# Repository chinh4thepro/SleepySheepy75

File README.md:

# SleepySheepy75

Making a keyboard cause im bored

## Hardware

Uses a soldered on rp2040 as the MCU
- 85x diodes for each switch (one extra for knob switch)
- 1x rotary encoder (EC11(E))
- 84x hotswap sockets
- 1x W25Q128JVS as flash rom
- 1x USB-C as connector 
- 2x buttons for "boot" selection
- Other stuff for electrical stuff

## Software

It is to be ported to QMK and be supported with VIA/VIAL

## Design

TODO - Probably going to happen when I get the pcb, case is going to be available in variety of materials

## Progress

- [x] Design the schematic (Done on 2023-09-08)
- [x] Come up with a name + Design logo (Done on 2023-10-07 (Scrapped on PCB though))
- [x] Design the PCB (Done on 2023-09-17)
- [ ] Order the PCB and its parts
- [ ] Construct PCB
- [ ] Port QMK + VIA/VIAL
- [ ] Design case for a 3d printer
- [ ] Design case for acrylic stacking
- [ ] Design case for metal CNC

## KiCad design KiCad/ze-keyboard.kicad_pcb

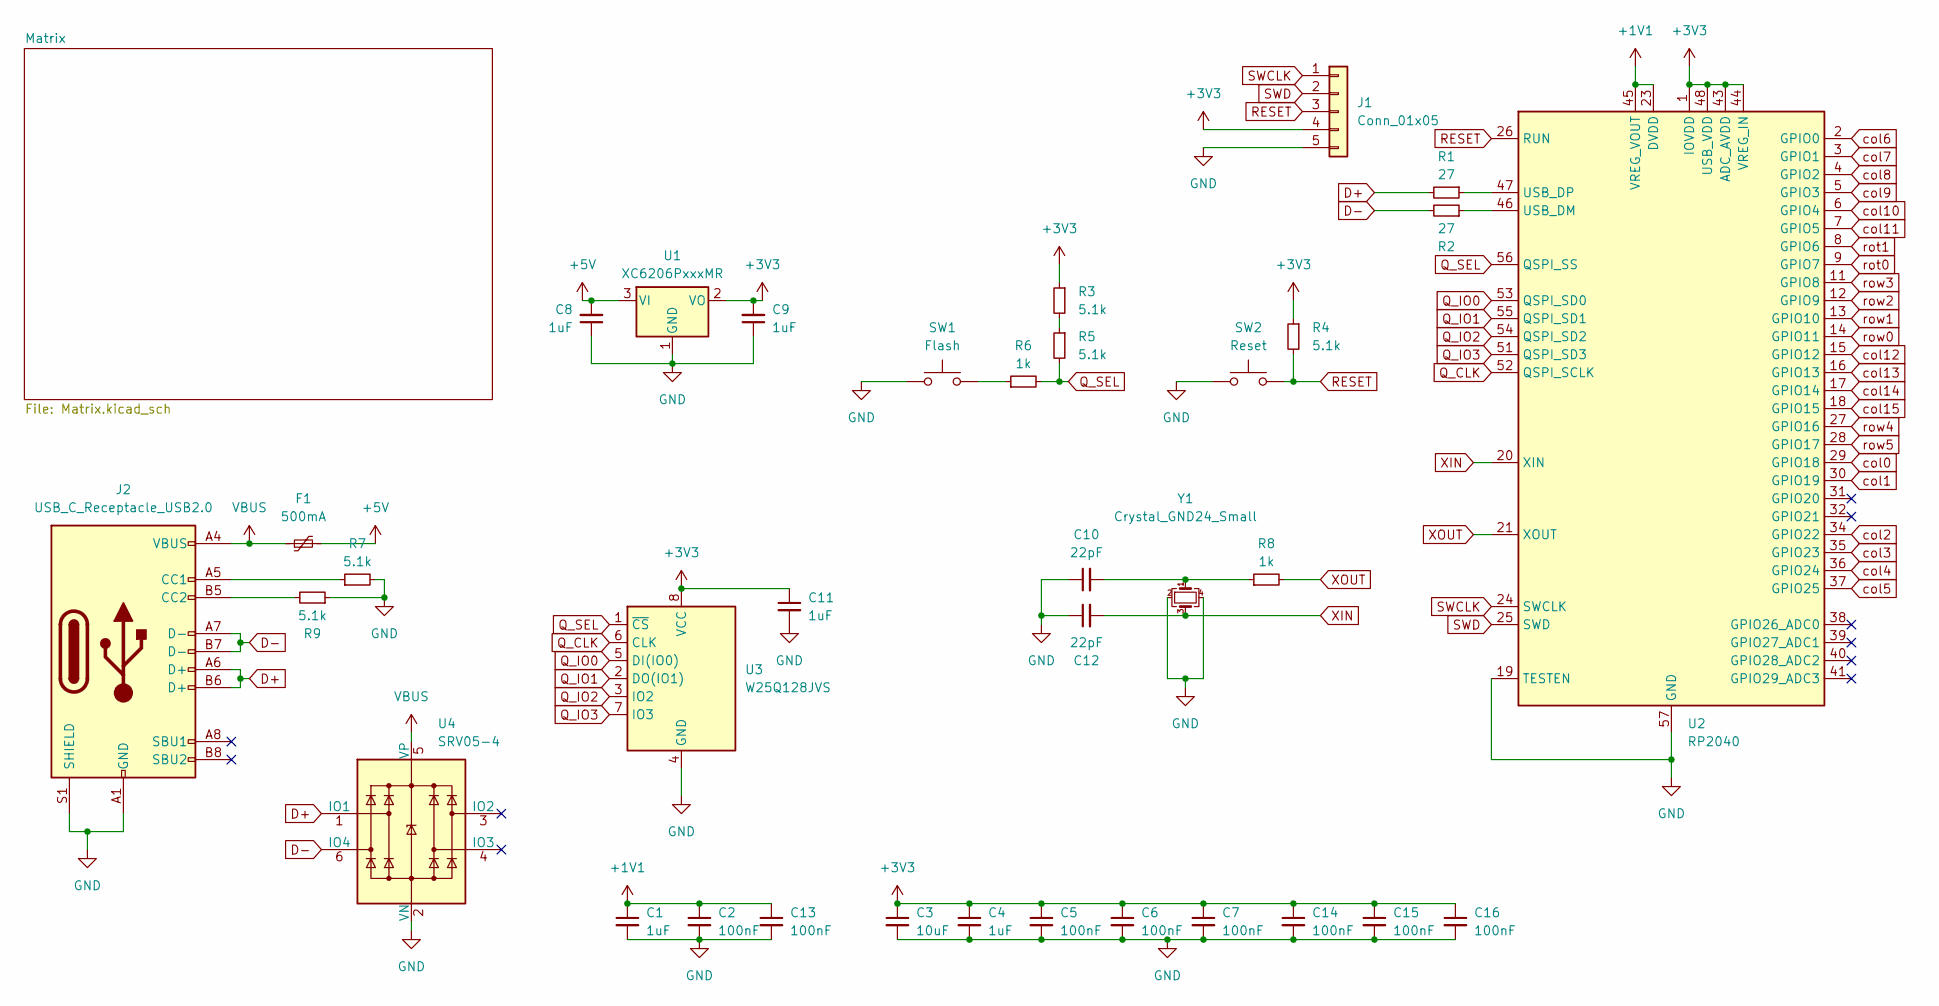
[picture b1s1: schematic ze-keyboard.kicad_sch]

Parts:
C1, C4, C8, C9, C11: 1uF; C_0402_1005Metric
C2, C5, C6, C7, C13, C14, C15, C16: 100nF; C_0402_1005Metric
C3: 10uF; C_0603_1608Metric
C10, C12: 22pF; C_0402_1005Metric
F1: 500mA; Fuse_1206_3216Metric
J1: Conn_01x05; PinHeader_1x05_P2.54mm_Vertical
J2: USB_C_Receptacle_USB2.0; USB_C_Receptacle_HRO_TYPE-C-31-M-12
R1, R2: 27; R_0402_1005Metric
R3, R4, R5, R7, R9: 5.1k; R_0402_1005Metric
R6, R8: 1k; R_0402_1005Metric
SW1: Flash; SW_SPST_TL3342
SW2: Reset; SW_SPST_TL3342
U1: XC6206PxxxMR; SOT-23-3
U2: RP2040; QFN-56-1EP_7x7mm_P0.4mm_EP3.2x3.2mm
U3: W25Q128JVS; SOIC-8_5.23x5.23mm_P1.27mm
U4: SRV05-4; SOT-23-6-routable
Y1: Crystal_GND24_Small; Crystal_SMD_3225-4Pin_3.2x2.5mm

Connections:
+1V1: C1.1, C2.1, C13.1, U2.23 (DVDD), U2.45 (VREG_VOUT), U2.50 (DVDD)
+3V3: C3.1, C4.1, C5.1, C6.1, C7.1, C9.2, C11.1, C14.1, C15.1, C16.1, J1.4, R3.1, R4.1, U1.2 (VO), U2.1 (IOVDD), U2.10 (IOVDD), U2.22 (IOVDD), U2.33 (IOVDD), U2.42 (IOVDD), U2.43 (ADC_AVDD), U2.44 (VREG_IN), U2.48 (USB_VDD), U2.49 (IOVDD), U3.8 (VCC)
+5V: C8.2, F1.2, U1.3 (VI); also elsewhere on the board
D+: J2.A6 (D+), J2.B6 (D+), R1.2, U4.1 (IO1)
D-: J2.A7 (D-), J2.B7 (D-), R2.2, U4.6 (IO4)
GND: C1.2, C2.2, C3.2, C4.2, C5.2, C6.2, C7.2, C8.1, C9.1, C10.1, C11.2, C12.1, C13.2, C14.2, C15.2, C16.2, J1.5, J2.A1 (GND), J2.A12 (GND), J2.B1 (GND), J2.B12 (GND), J2.S1 (SHIELD), R7.2, R9.1, SW1.1, SW2.1, U1.1 (GND), U2.19 (TESTEN), U2.57 (GND), U3.4 (GND), U4.2 (VN), Y1.2, Y1.4; also elsewhere on the board
unnamed: C10.2, R8.1, Y1.1
unnamed: J2.A5 (CC1), R7.1
unnamed: J2.B5 (CC2), R9.2
unnamed: R3.2, R5.1
unnamed: R6.1, SW1.2
unnamed: R2.1, U2.46 (USB_DM)
unnamed: R1.1, U2.47 (USB_DP)
Q_CLK: U2.52 (QSPI_SCLK), U3.6 (CLK)
Q_IO0: U2.53 (QSPI_SD0), U3.5 (DI(IO0))
Q_IO1: U2.55 (QSPI_SD1), U3.2 (DO(IO1))
Q_IO2: U2.54 (QSPI_SD2), U3.3 (IO2)
Q_IO3: U2.51 (QSPI_SD3), U3.7 (IO3)
Q_SEL: R5.2, R6.2, U2.56 (QSPI_SS), U3.1 (~CS)
RESET: J1.3, R4.2, SW2.2, U2.26 (RUN)
SWCLK: J1.1, U2.24 (SWCLK)
SWD: J1.2, U2.25 (SWD)
VBUS: F1.1, J2.A4 (VBUS), J2.A9 (VBUS), J2.B4 (VBUS), J2.B9 (VBUS), U4.5 (VP)
XIN: C12.2, U2.20 (XIN), Y1.3
XOUT: R8.2, U2.21 (XOUT)
col0: U2.29 (GPIO18); also elsewhere on the board
col1: U2.30 (GPIO19); also elsewhere on the board
col2: U2.34 (GPIO22); also elsewhere on the board
col3: U2.35 (GPIO23); also elsewhere on the board
col4: U2.36 (GPIO24); also elsewhere on the board
col5: U2.37 (GPIO25); also elsewhere on the board
col6: U2.2 (GPIO0); also elsewhere on the board
col7: U2.3 (GPIO1); also elsewhere on the board
col8: U2.4 (GPIO2); also elsewhere on the board
col9: U2.5 (GPIO3); also elsewhere on the board
col10: U2.6 (GPIO4); also elsewhere on the board
col11: U2.7 (GPIO5); also elsewhere on the board
col12: U2.15 (GPIO12); also elsewhere on the board
col13: U2.16 (GPIO13); also elsewhere on the board
col14: U2.17 (GPIO14); also elsewhere on the board
col15: U2.18 (GPIO15); also elsewhere on the board
row0: U2.14 (GPIO11); also elsewhere on the board
row1: U2.13 (GPIO10); also elsewhere on the board
row2: U2.12 (GPIO9); also elsewhere on the board
row3: U2.11 (GPIO8); also elsewhere on the board
row4: U2.27 (GPIO16); also elsewhere on the board
row5: U2.28 (GPIO17); also elsewhere on the board

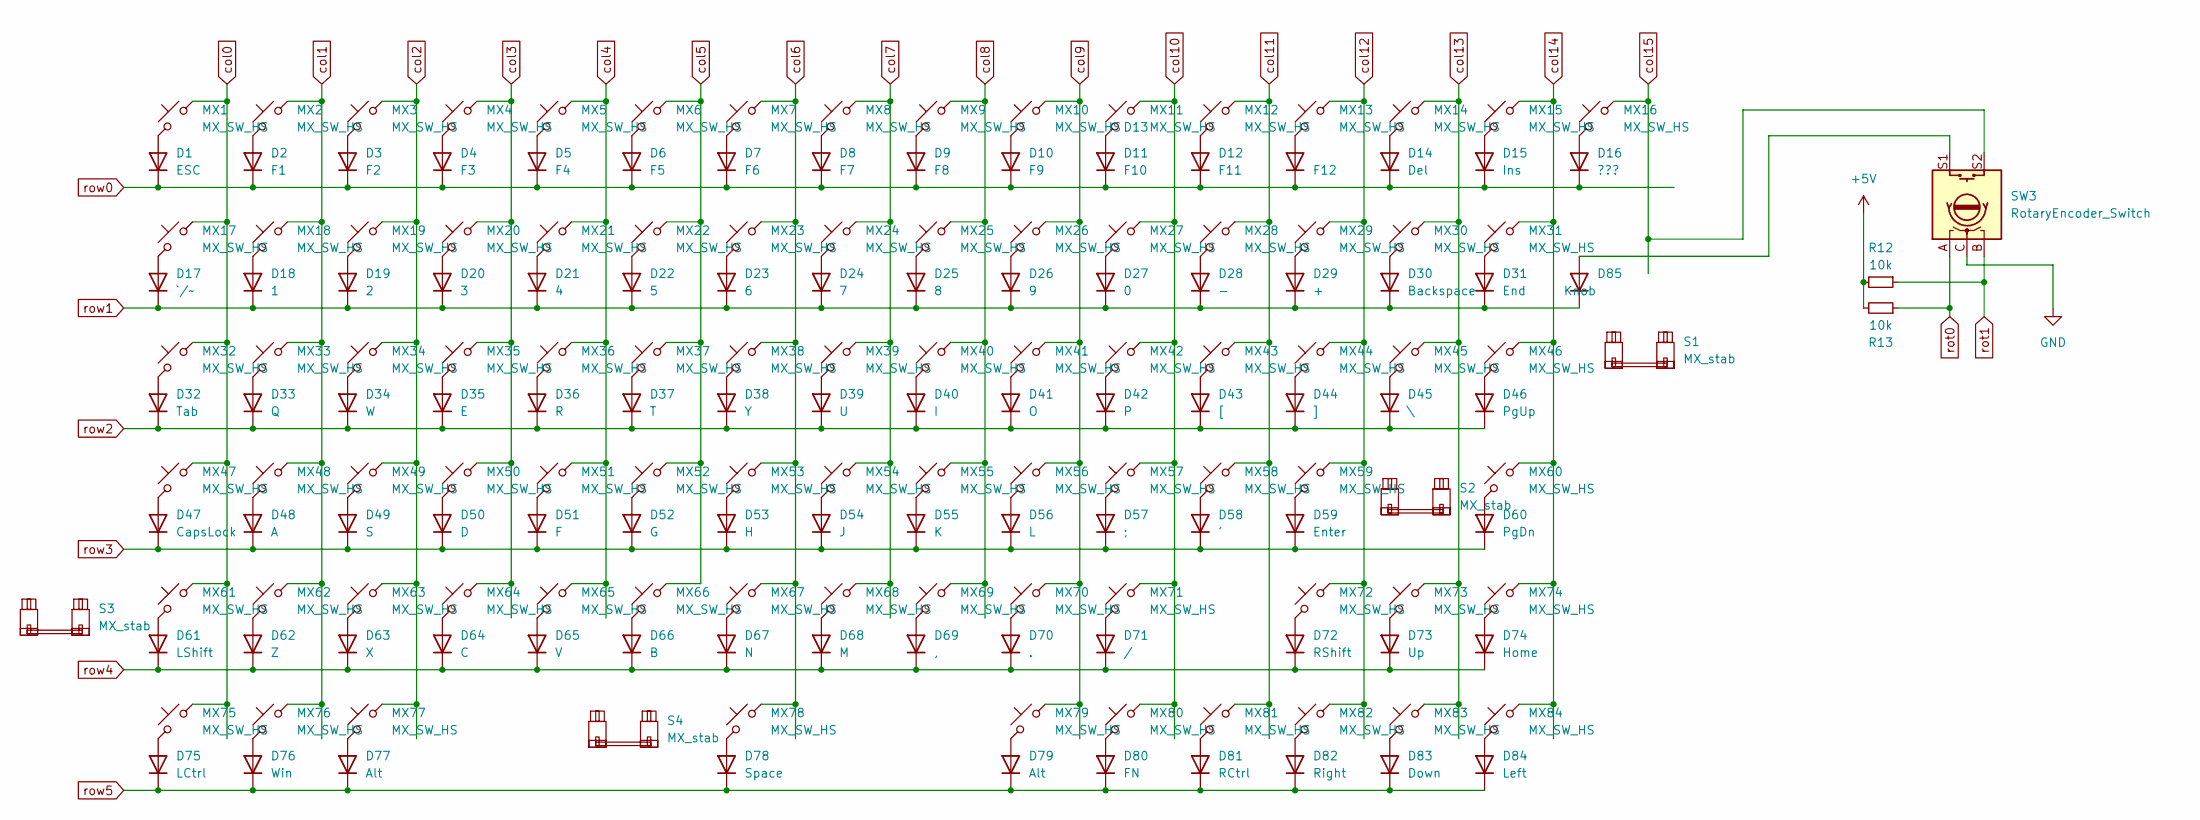
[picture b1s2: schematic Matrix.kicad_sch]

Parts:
D1: ESC; D_SOD-123
D2: F1; D_SOD-123
D3: F2; D_SOD-123
D4: F3; D_SOD-123
D5: F4; D_SOD-123
D6: F5; D_SOD-123
D7: F6; D_SOD-123
D8: F7; D_SOD-123
D9: F8; D_SOD-123
D10: F9; D_SOD-123
D11: F10; D_SOD-123
D12: F11; D_SOD-123
D13: F12; D_SOD-123
D14: Del; D_SOD-123
D15: Ins; D_SOD-123
D16: ???; D_SOD-123
D17: `/~; D_SOD-123
D18: 1; D_SOD-123
D19: 2; D_SOD-123
D20: 3; D_SOD-123
D21: 4; D_SOD-123
D22: 5; D_SOD-123
D23: 6; D_SOD-123
D24: 7; D_SOD-123
D25: 8; D_SOD-123
D26: 9; D_SOD-123
D27: 0; D_SOD-123
D28: -; D_SOD-123
D29: +; D_SOD-123
D30: Backspace; D_SOD-123
D31: End; D_SOD-123
D32: Tab; D_SOD-123
D33: Q; D_SOD-123
D34: W; D_SOD-123
D35: E; D_SOD-123
D36: R; D_SOD-123
D37: T; D_SOD-123
D38: Y; D_SOD-123
D39: U; D_SOD-123
D40: I; D_SOD-123
D41: O; D_SOD-123
D42: P; D_SOD-123
D43: [; D_SOD-123
D44: ]; D_SOD-123
D45: \; D_SOD-123
D46: PgUp; D_SOD-123
D47: CapsLock; D_SOD-123
D48: A; D_SOD-123
D49: S; D_SOD-123
D50: D; D_SOD-123
D51: F; D_SOD-123
D52: G; D_SOD-123
D53: H; D_SOD-123
D54: J; D_SOD-123
D55: K; D_SOD-123
D56: L; D_SOD-123
D57: ;; D_SOD-123
D58: '; D_SOD-123
D59: Enter; D_SOD-123
D60: PgDn; D_SOD-123
D61: LShift; D_SOD-123
D62: Z; D_SOD-123
D63: X; D_SOD-123
D64: C; D_SOD-123
D65: V; D_SOD-123
D66: B; D_SOD-123
D67: N; D_SOD-123
D68: M; D_SOD-123
D69: ,; D_SOD-123
D70: .; D_SOD-123
D71: /; D_SOD-123
D72: RShift; D_SOD-123
D73: Up; D_SOD-123
D74: Home; D_SOD-123
D75: LCtrl; D_SOD-123
D76: Win; D_SOD-123
D77, D79: Alt; D_SOD-123
D78: Space; D_SOD-123
D80: FN; D_SOD-123
D81: RCtrl; D_SOD-123
D82: Right; D_SOD-123
D83: Down; D_SOD-123
D84: Left; D_SOD-123
D85: Knob; D_SOD-123
MX1, MX2, MX3, MX4, MX5, MX6, MX7, MX8, MX9, MX10, MX11, MX12, MX13, MX14, MX15, MX16, MX17, MX18, MX19, MX20, MX21, MX22, MX23, MX24, MX25, MX26, MX27, MX28, MX29, MX30, MX31, MX32, MX33, MX34, MX35, MX36, MX37, MX38, MX39, MX40, MX41, MX42, MX43, MX44, MX45, MX46, MX47, MX48, MX49, MX50, MX51, MX52, MX53, MX54, MX55, MX56, MX57, MX58, MX59, MX60, MX61, MX62, MX63, MX64, MX65, MX66, MX67, MX68, MX69, MX70, MX71, MX72, MX73, MX74, MX75, MX76, MX77, MX78, MX79, MX80, MX81, MX82, MX83, MX84: MX_SW_HS; SW_MX_HS_1u
R12, R13: 10k; R_0402_1005Metric
S1, S2, S3: MX_stab; STAB_MX_P_2u
S4: MX_stab; STAB_MX_P_6.25u
SW3: RotaryEncoder_Switch; RotaryEncoder_Alps_EC11E-Switch_Vertical_H20mm

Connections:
+5V: R12.2; also elsewhere on the board
GND: SW3.C; also elsewhere on the board
unnamed: D1.2 (A), MX1.1
unnamed: D2.2 (A), MX2.1
unnamed: D3.2 (A), MX3.1
unnamed: D4.2 (A), MX4.1
unnamed: D5.2 (A), MX5.1
unnamed: D6.2 (A), MX6.1
unnamed: D7.2 (A), MX7.1
unnamed: D8.2 (A), MX8.1
unnamed: D9.2 (A), MX9.1
unnamed: D10.2 (A), MX10.1
unnamed: D11.2 (A), MX11.1
unnamed: D12.2 (A), MX12.1
unnamed: D13.2 (A), MX13.1
unnamed: D14.2 (A), MX14.1
unnamed: D15.2 (A), MX15.1
unnamed: D16.2 (A), MX16.1
unnamed: D17.2 (A), MX17.1
unnamed: D18.2 (A), MX18.1
unnamed: D19.2 (A), MX19.1
unnamed: D20.2 (A), MX20.1
unnamed: D21.2 (A), MX21.1
unnamed: D22.2 (A), MX22.1
unnamed: D23.2 (A), MX23.1
unnamed: D24.2 (A), MX24.1
unnamed: D25.2 (A), MX25.1
unnamed: D26.2 (A), MX26.1
unnamed: D27.2 (A), MX27.1
unnamed: D28.2 (A), MX28.1
unnamed: D29.2 (A), MX29.1
unnamed: D30.2 (A), MX30.1
unnamed: D31.2 (A), MX31.1
unnamed: D32.2 (A), MX32.1
unnamed: D33.2 (A), MX33.1
unnamed: D34.2 (A), MX34.1
unnamed: D35.2 (A), MX35.1
unnamed: D36.2 (A), MX36.1
unnamed: D37.2 (A), MX37.1
unnamed: D38.2 (A), MX38.1
unnamed: D39.2 (A), MX39.1
unnamed: D40.2 (A), MX40.1
unnamed: D41.2 (A), MX41.1
unnamed: D42.2 (A), MX42.1
unnamed: D43.2 (A), MX43.1
unnamed: D44.2 (A), MX44.1
unnamed: D45.2 (A), MX45.1
unnamed: D46.2 (A), MX46.1
unnamed: D47.2 (A), MX47.1
unnamed: D48.2 (A), MX48.1
unnamed: D49.2 (A), MX49.1
unnamed: D50.2 (A), MX50.1
unnamed: D51.2 (A), MX51.1
unnamed: D52.2 (A), MX52.1
unnamed: D53.2 (A), MX53.1
unnamed: D54.2 (A), MX54.1
unnamed: D55.2 (A), MX55.1
unnamed: D56.2 (A), MX56.1
unnamed: D57.2 (A), MX57.1
unnamed: D58.2 (A), MX58.1
unnamed: D59.2 (A), MX59.1
unnamed: D60.2 (A), MX60.1
unnamed: D61.2 (A), MX61.1
unnamed: D62.2 (A), MX62.1
unnamed: D63.2 (A), MX63.1
unnamed: D64.2 (A), MX64.1
unnamed: D65.2 (A), MX65.1
unnamed: D66.2 (A), MX66.1
unnamed: D67.2 (A), MX67.1
unnamed: D68.2 (A), MX68.1
unnamed: D69.2 (A), MX69.1
unnamed: D70.2 (A), MX70.1
unnamed: D71.2 (A), MX71.1
unnamed: D72.2 (A), MX72.1
unnamed: D73.2 (A), MX73.1
unnamed: D74.2 (A), MX74.1
unnamed: D75.2 (A), MX75.1
unnamed: D76.2 (A), MX76.1
unnamed: D77.2 (A), MX77.1
unnamed: D78.2 (A), MX78.1
unnamed: D79.2 (A), MX79.1
unnamed: D80.2 (A), MX80.1
unnamed: D81.2 (A), MX81.1
unnamed: D82.2 (A), MX82.1
unnamed: D83.2 (A), MX83.1
unnamed: D84.2 (A), MX84.1
unnamed: D85.2 (A), SW3.S1
col0: MX1.2, MX17.2, MX32.2, MX47.2, MX61.2, MX75.2; also elsewhere on the board
col1: MX2.2, MX18.2, MX33.2, MX48.2, MX62.2, MX76.2; also elsewhere on the board
col2: MX3.2, MX19.2, MX34.2, MX49.2, MX63.2, MX77.2; also elsewhere on the board
col3: MX4.2, MX20.2, MX35.2, MX50.2, MX64.2; also elsewhere on the board
col4: MX5.2, MX21.2, MX36.2, MX51.2, MX65.2; also elsewhere on the board
col5: MX6.2, MX22.2, MX37.2, MX52.2, MX66.2; also elsewhere on the board
col6: MX7.2, MX23.2, MX38.2, MX53.2, MX67.2, MX78.2; also elsewhere on the board
col7: MX8.2, MX24.2, MX39.2, MX54.2, MX68.2; also elsewhere on the board
col8: MX9.2, MX25.2, MX40.2, MX55.2, MX69.2; also elsewhere on the board
col9: MX10.2, MX26.2, MX41.2, MX56.2, MX70.2, MX79.2; also elsewhere on the board
col10: MX11.2, MX27.2, MX42.2, MX57.2, MX71.2, MX80.2; also elsewhere on the board
col11: MX12.2, MX28.2, MX43.2, MX58.2, MX81.2; also elsewhere on the board
col12: MX13.2, MX29.2, MX44.2, MX59.2, MX72.2, MX82.2; also elsewhere on the board
col13: MX14.2, MX30.2, MX45.2, MX73.2, MX83.2; also elsewhere on the board
col14: MX15.2, MX31.2, MX46.2, MX60.2, MX74.2, MX84.2; also elsewhere on the board
col15: MX16.2, SW3.S2; also elsewhere on the board
row0: D1.1 (K), D2.1 (K), D3.1 (K), D4.1 (K), D5.1 (K), D6.1 (K), D7.1 (K), D8.1 (K), D9.1 (K), D10.1 (K), D11.1 (K), D12.1 (K), D13.1 (K), D14.1 (K), D15.1 (K), D16.1 (K); also elsewhere on the board
row1: D17.1 (K), D18.1 (K), D19.1 (K), D20.1 (K), D21.1 (K), D22.1 (K), D23.1 (K), D24.1 (K), D25.1 (K), D26.1 (K), D27.1 (K), D28.1 (K), D29.1 (K), D30.1 (K), D31.1 (K), D85.1 (K); also elsewhere on the board
row2: D32.1 (K), D33.1 (K), D34.1 (K), D35.1 (K), D36.1 (K), D37.1 (K), D38.1 (K), D39.1 (K), D40.1 (K), D41.1 (K), D42.1 (K), D43.1 (K), D44.1 (K), D45.1 (K), D46.1 (K); also elsewhere on the board
row3: D47.1 (K), D48.1 (K), D49.1 (K), D50.1 (K), D51.1 (K), D52.1 (K), D53.1 (K), D54.1 (K), D55.1 (K), D56.1 (K), D57.1 (K), D58.1 (K), D59.1 (K), D60.1 (K); also elsewhere on the board
row4: D61.1 (K), D62.1 (K), D63.1 (K), D64.1 (K), D65.1 (K), D66.1 (K), D67.1 (K), D68.1 (K), D69.1 (K), D70.1 (K), D71.1 (K), D72.1 (K), D73.1 (K), D74.1 (K); also elsewhere on the board
row5: D75.1 (K), D76.1 (K), D77.1 (K), D78.1 (K), D79.1 (K), D80.1 (K), D81.1 (K), D82.1 (K), D83.1 (K), D84.1 (K); also elsewhere on the board

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
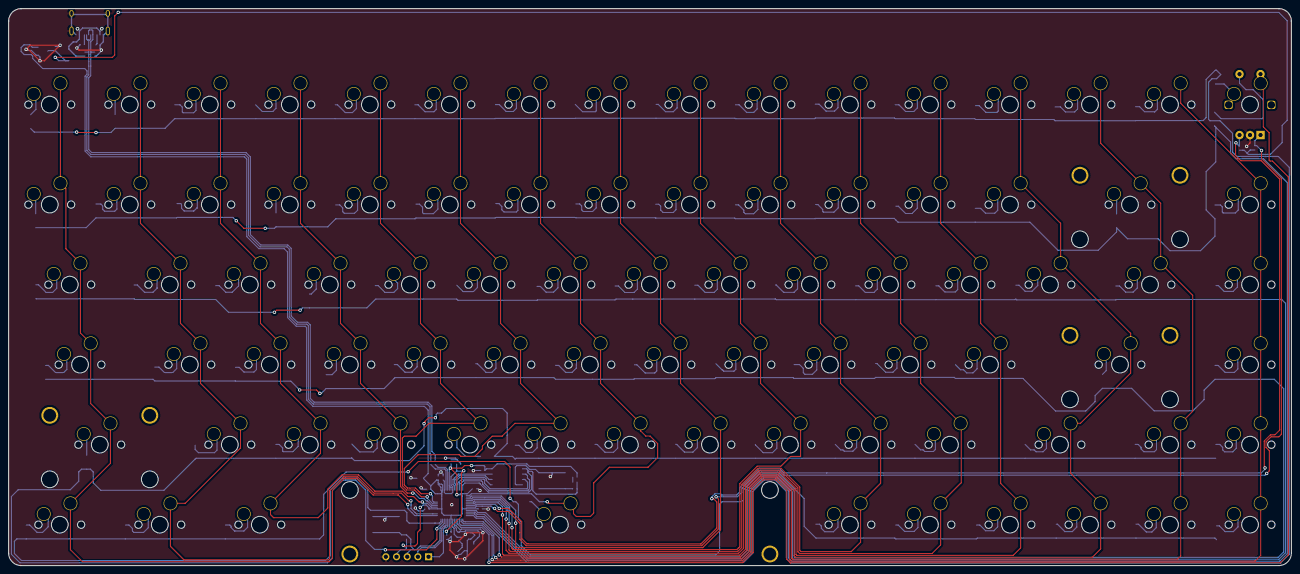
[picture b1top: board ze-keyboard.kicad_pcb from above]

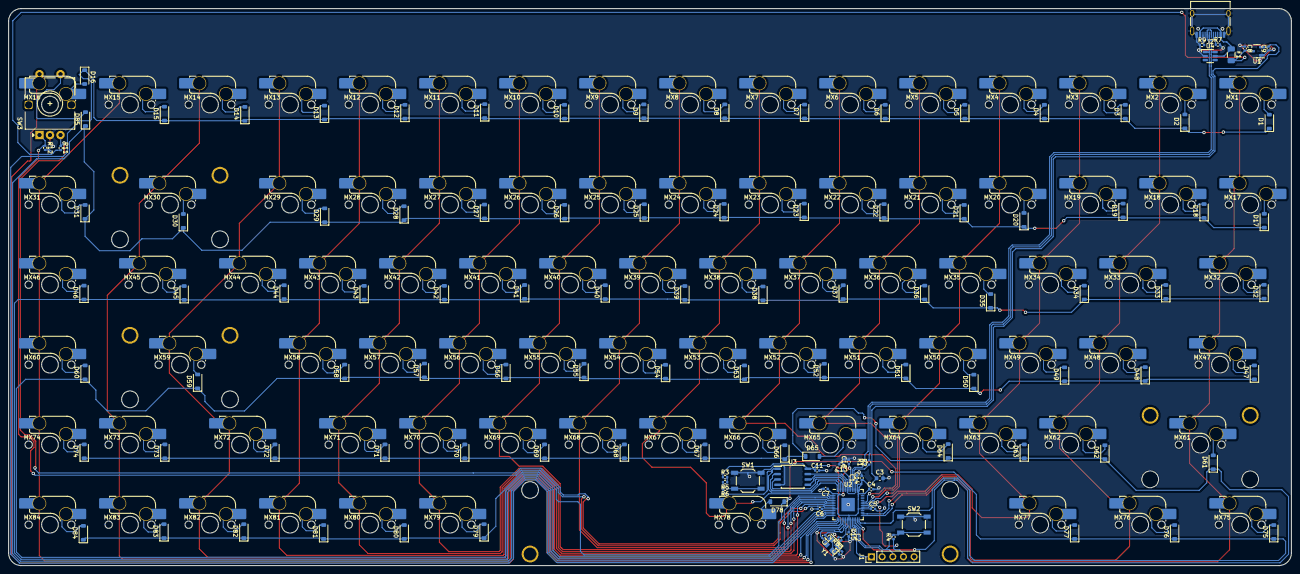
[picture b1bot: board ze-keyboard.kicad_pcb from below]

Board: 2 copper layers, 305.4 x 132.6 mm, 211 parts (211 on the bottom side), 134 nets.

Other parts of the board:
R11: 10k; R_0402_1005Metric

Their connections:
+5V: R11.2; also elsewhere on the board

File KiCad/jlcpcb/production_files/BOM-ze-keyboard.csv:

Comment,Designator,Footprint,LCSC
1k,"R6,R8",R_0402_1005Metric,C11702
100nF,"C13,C14,C15,C16,C2,C5,C6,C7",C_0402_1005Metric,C1525
10uF,C3,C_0603_1608Metric,C15525
22pF,"C10,C12",C_0402_1005Metric,C1555
USB_C_Receptacle_USB2.0,J2,USB_C_Receptacle_HRO_TYPE-C-31-M-12,C165948
RP2040,U2,QFN-56-1EP_7x7mm_P0.4mm_EP3.2x3.2mm,C2040
500mA,F1,Fuse_1206_3216Metric,C20798
10k,"R11,R12",R_0402_1005Metric,C25744
27,"R1,R2",R_0402_1005Metric,C25771
5.1k,"R3,R4,R5,R7,R9",R_0402_1005Metric,C25905
Flash,"SW1,SW2",SW_SPST_TL3342,C318884
RotaryEncoder_Switch,SW3,RotaryEncoder_Alps_EC11E-Switch_Vertical_H20mm,C470710
MX_SW_HS,"MX1,MX10,MX11,MX12,MX13,MX14,MX15,MX16,MX17,MX18,MX19,MX2,MX20,MX21,MX22,MX23,MX24,MX25,MX26,MX27,MX28,MX29,MX3,MX30,MX31,MX32,MX33,MX34,MX35,MX36,MX37,MX38,MX39,MX4,MX40,MX41,MX42,MX43,MX44,MX45,MX46,MX47,MX48,MX49,MX5,MX50,MX51,MX52,MX53,MX54,MX55,MX56,MX57,MX58,MX59,MX6,MX60,MX61,MX62,MX63,MX64,MX65,MX66,MX67,MX68,MX69,MX7,MX70,MX71,MX72,MX73,MX74,MX75,MX76,MX77,MX78,MX79,MX8,MX80,MX81,MX82,MX83,MX84,MX9",SW_MX_HS_1u,C5156480
1uF,"C1,C11,C4,C8,C9",C_0402_1005Metric,C52923
XC6206PxxxMR,U1,SOT-23-3,C5446
Crystal_GND24_Small,Y1,Crystal_SMD_3225-4Pin_3.2x2.5mm,C5765981
ESC,"D1,D10,D11,D12,D13,D14,D15,D16,D17,D18,D19,D2,D20,D21,D22,D23,D24,D25,D26,D27,D28,D29,D3,D30,D31,D32,D33,D34,D35,D36,D37,D38,D39,D4,D40,D41,D42,D43,D44,D45,D46,D47,D48,D49,D5,D50,D51,D52,D53,D54,D55,D56,D57,D58,D59,D6,D60,D61,D62,D63,D64,D65,D66,D67,D68,D69,D7,D70,D71,D72,D73,D74,D75,D76,D77,D78,D79,D8,D80,D81,D82,D83,D84,D85,D9",D_SOD-123,C81598
SRV05-4,U4,SOT-23-6-routable,C85364
W25Q128JVS,U3,SOIC-8_5.23x5.23mm_P1.27mm,C97521

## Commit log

2023-09-08 Add kicad files
2023-09-08 add submodules
2023-09-08 move files out of directory
2023-09-08 remove the directory
2023-09-08 reset submodules
2023-09-08 readd submodules
2023-09-09 move kicad stuff into the directory again and add Plate
2023-09-09 remove clutter from the root
2023-09-09 reset submodules, AGAIN
2023-09-09 add modules again
2023-09-09 "finish" the keyboard schematics
2023-09-09 add plate 3d model
2023-09-09 add split plate
2023-09-11 fix stuff... i forgot the other stuff i added
2023-09-12 fix flipped keyboard, and finish routing mcu
2023-09-12 add traces to diodes to their respective switches, and fix holes on knob
2023-09-12 do some tracing
2023-09-13 finish pcb
2023-09-13 update jlbpcb stuff
2023-09-13 i forgor what i added
2023-09-13 remove funny svgs
2023-09-14 do some more stuff like fixing most of 90 degree traces
2023-09-14 some changes, a bit more jlcpcb stuff
2023-09-14 MORE JCBPCB STUFF
2023-09-15 jlcpcb stuff
2023-09-16 stuff
2023-09-16 PCB AND JLCPCB STUFF DONE!!!
2023-09-17 fix zones not filling
2023-09-17 more jlcpcb stuff
2023-09-19 Add MIT License
2023-09-19 Update README, based off of Sheepy0125/AlarmClock's readme
2023-09-19 fix typo in readme
2023-09-28 rename files
2023-09-28 update readme for the new repo name
2023-10-07 add the logo/images
